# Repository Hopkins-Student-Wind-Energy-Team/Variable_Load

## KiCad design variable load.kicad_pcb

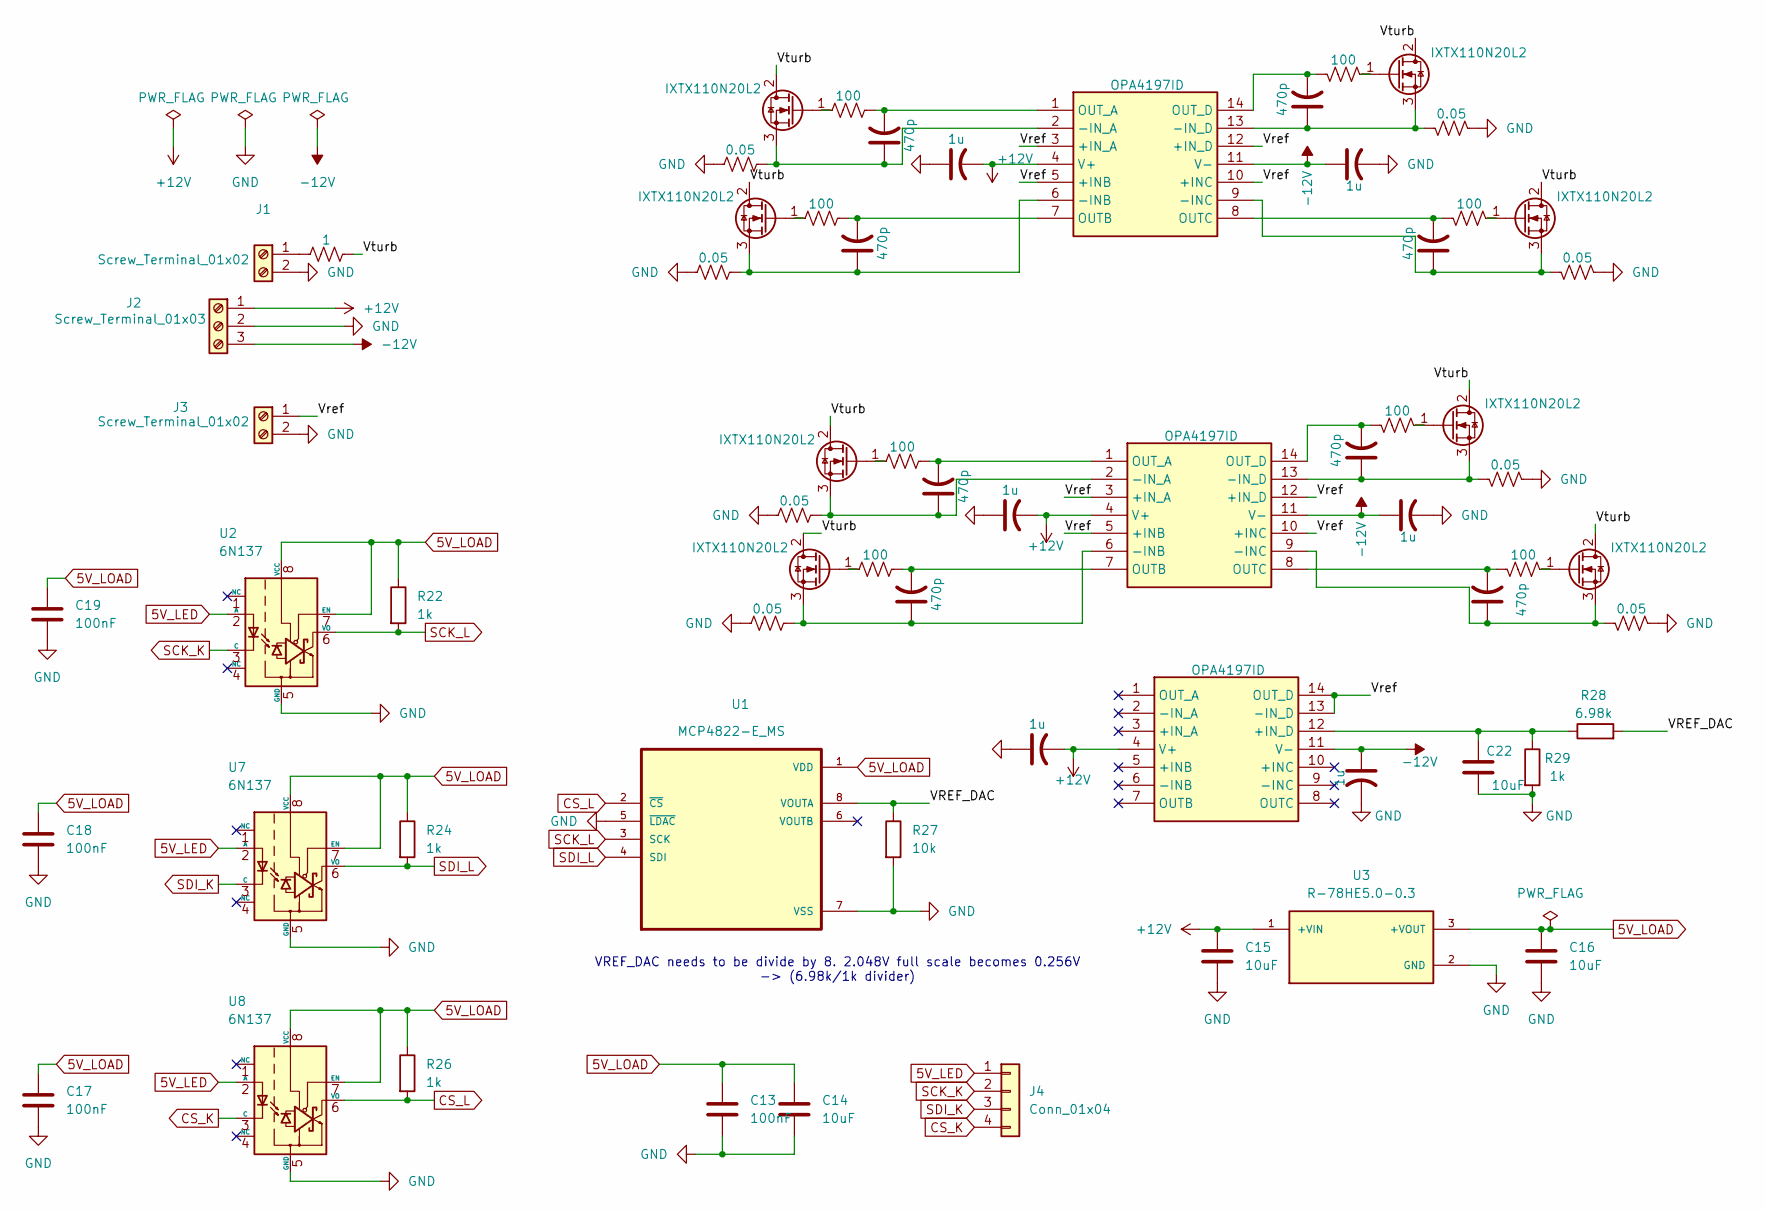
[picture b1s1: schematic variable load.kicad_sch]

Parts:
C1, C2, C9, C11, C20, C21: 1u; C_0805_2012Metric
C3, C4, C5, C6, C7, C8, C10, C12: 470p; C_0805_2012Metric
C13, C17, C18, C19: 100nF; C_0805_2012Metric
C14, C22: 10uF; C_1206_3216Metric
C15, C16: 10uF; SOIC-8_3.9x4.9mm_P1.27mm
IC1, IC2, IC3: OPA4197ID; SOIC-14_3.9x8.7mm_P1.27mm; Manufacturer_Part_Number OPA4172IDR; Mouser Part Number 595-OPA4172IDR
J1, J3: Screw_Terminal_01x02; TerminalBlock_Phoenix_MKDS-1,5-2_1x02_P5.00mm_Horizontal
J2: Screw_Terminal_01x03; TerminalBlock_Phoenix_MKDS-1,5-3_1x03_P5.00mm_Horizontal
J4: Conn_01x04; PinHeader_1x04_P2.54mm_Vertical
Q1, Q2, Q3, Q4, Q5, Q6, Q7, Q8: IXTX110N20L2; TO-247-3_Vertical
R1, R3, R5, R7, R9, R10, R14, R16: 0.05; R_2512_6332Metric
R2, R4, R6, R8, R11, R12, R13, R15: 100; R_0805_2012Metric
R17: 1; R_2512_6332Metric
R22, R24, R26, R29: 1k; R_0805_2012Metric
R27: 10k; R_0805_2012Metric
R28: 6.98k; R_0805_2012Metric
U1: MCP4822-E_MS; MSOP-8_3x3mm_P0.65mm
U2, U7, U8: 6N137; DIP-8_W7.62mm
U3: R-78HE5.0-0.3; SIP3_11.6x8.5mm; PARTREV 0/2019

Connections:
5V_LED: J4.1, U2.2 (A), U7.2 (A), U8.2 (A)
5V_LOAD: C13.1, C14.1, C16.1, C17.1, C18.1, C19.1, R22.1, R24.1, R26.1, U1.1 (VDD), U2.7 (EN), U2.8 (VCC), U3.3 (+VOUT), U7.7 (EN), U7.8 (VCC), U8.7 (EN), U8.8 (VCC)
+12V: C1.2, C9.2, C15.1, C20.2, IC1.4 (V+), IC2.4 (V+), IC3.4 (V+), J2.1, U3.1 (+VIN)
-12V: C2.1, C11.1, C21.1, IC1.11 (V-), IC2.11 (V-), IC3.11 (V-), J2.3
/VREF_DAC: R27.1, R28.2, U1.8 (VOUTA)
/Vref: IC1.3 (+IN_A), IC1.5 (+INB), IC1.10 (+INC), IC1.12 (+IN_D), IC2.3 (+IN_A), IC2.5 (+INB), IC2.10 (+INC), IC2.12 (+IN_D), IC3.13 (-IN_D), IC3.14 (OUT_D), J3.1
/Vturb: Q1.2 (D), Q2.2 (D), Q3.2 (D), Q4.2 (D), Q5.2 (D), Q6.2 (D), Q7.2 (D), Q8.2 (D), R17.1
CS_K: J4.4, U8.3 (C)
CS_L: R26.2, U1.2 (~CS), U8.6 (VO)
GND: C1.1, C2.2, C9.1, C11.2, C13.2, C14.2, C15.2, C16.2, C17.2, C18.2, C19.2, C20.1, C21.2, C22.2, J1.2, J2.2, J3.2, R1.2, R3.2, R5.2, R7.2, R9.2, R10.2, R14.2, R16.2, R27.2, R29.2, U1.5 (~LDAC), U1.7 (VSS), U2.5 (GND), U3.2 (GND), U7.5 (GND), U8.5 (GND)
unnamed: C4.1, IC1.6 (-INB), Q2.3 (S), R3.1
unnamed: C5.1, IC1.9 (-INC), Q3.3 (S), R5.1
unnamed: C3.1, IC1.2 (-IN_A), Q1.3 (S), R1.1
unnamed: C6.1, IC1.13 (-IN_D), Q4.3 (S), R7.1
unnamed: C4.2, IC1.7 (OUTB), R4.1
unnamed: C5.2, IC1.8 (OUTC), R6.1
unnamed: C3.2, IC1.1 (OUT_A), R2.1
unnamed: C6.2, IC1.14 (OUT_D), R8.1
unnamed: C7.1, IC2.6 (-INB), Q5.3 (S), R9.1
unnamed: C12.1, IC2.9 (-INC), Q8.3 (S), R16.1
unnamed: C8.1, IC2.2 (-IN_A), Q6.3 (S), R10.1
unnamed: C10.1, IC2.13 (-IN_D), Q7.3 (S), R14.1
unnamed: C7.2, IC2.7 (OUTB), R11.1
unnamed: C12.2, IC2.8 (OUTC), R15.1
unnamed: C8.2, IC2.1 (OUT_A), R12.1
unnamed: C10.2, IC2.14 (OUT_D), R13.1
unnamed: C22.1, IC3.12 (+IN_D), R28.1, R29.1
unnamed: J1.1, R17.2
unnamed: Q1.1 (G), R2.2
unnamed: Q2.1 (G), R4.2
unnamed: Q3.1 (G), R6.2
unnamed: Q4.1 (G), R8.2
unnamed: Q5.1 (G), R11.2
unnamed: Q6.1 (G), R12.2
unnamed: Q7.1 (G), R13.2
unnamed: Q8.1 (G), R15.2
SCK_K: J4.2, U2.3 (C)
SCK_L: R22.2, U1.3 (SCK), U2.6 (VO)
SDI_K: J4.3, U7.3 (C)
SDI_L: R24.2, U1.4 (SDI), U7.6 (VO)

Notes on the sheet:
VREF_DAC needs to be divide by 8. 2.048V full scale becomes 0.256V -> (6.98k/1k divider)

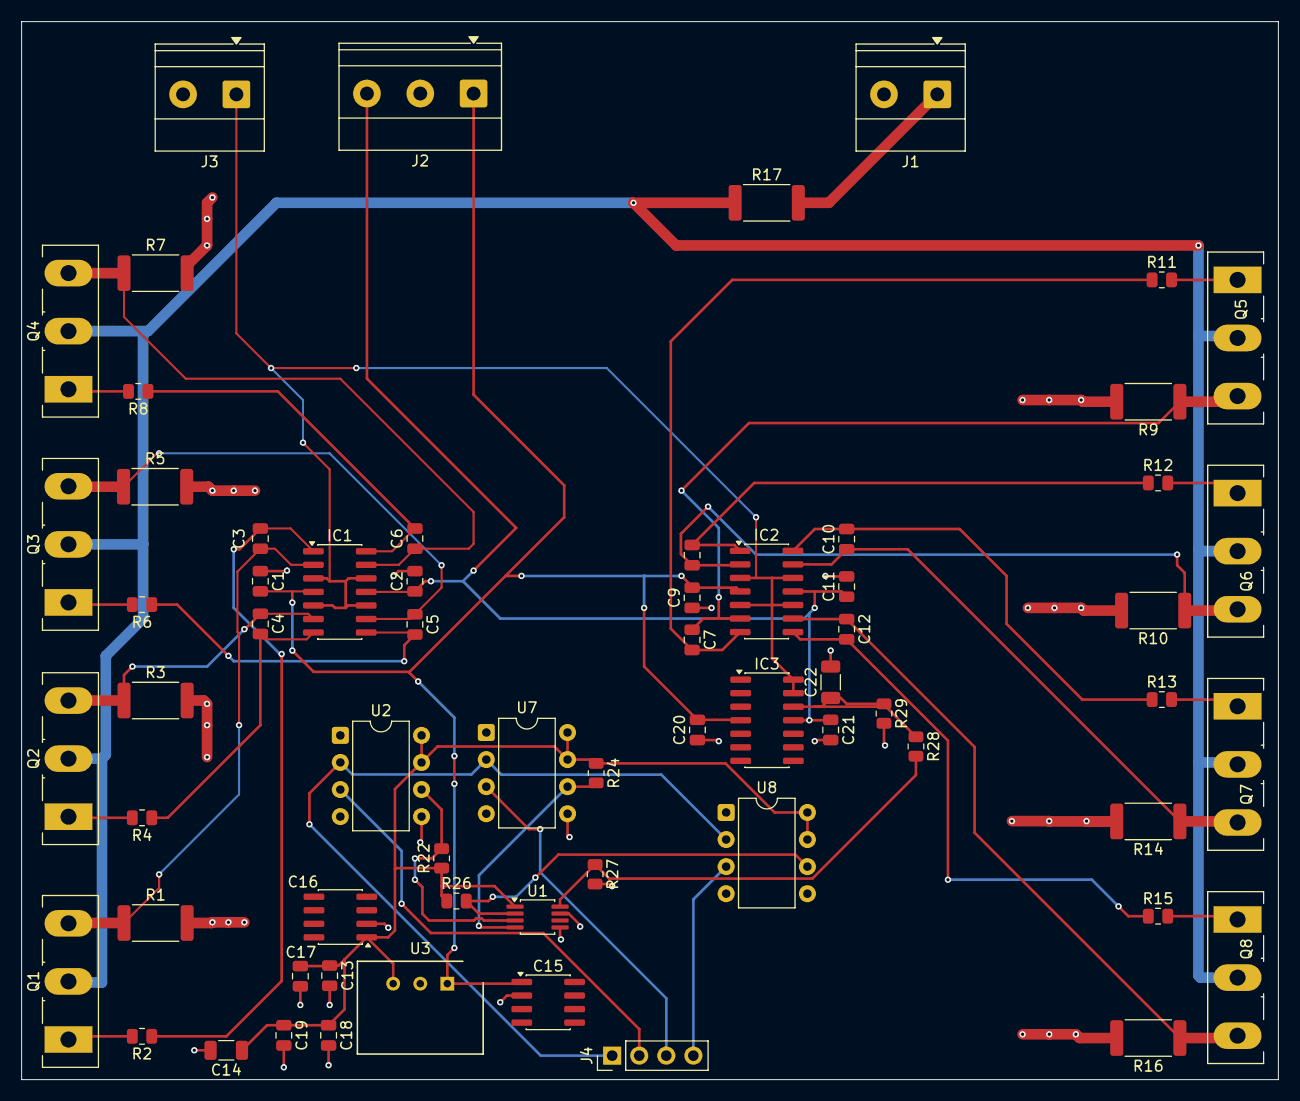
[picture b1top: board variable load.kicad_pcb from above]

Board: 2 copper layers, 117.9 x 99.2 mm, 65 parts (0 on the bottom side), 40 nets.
